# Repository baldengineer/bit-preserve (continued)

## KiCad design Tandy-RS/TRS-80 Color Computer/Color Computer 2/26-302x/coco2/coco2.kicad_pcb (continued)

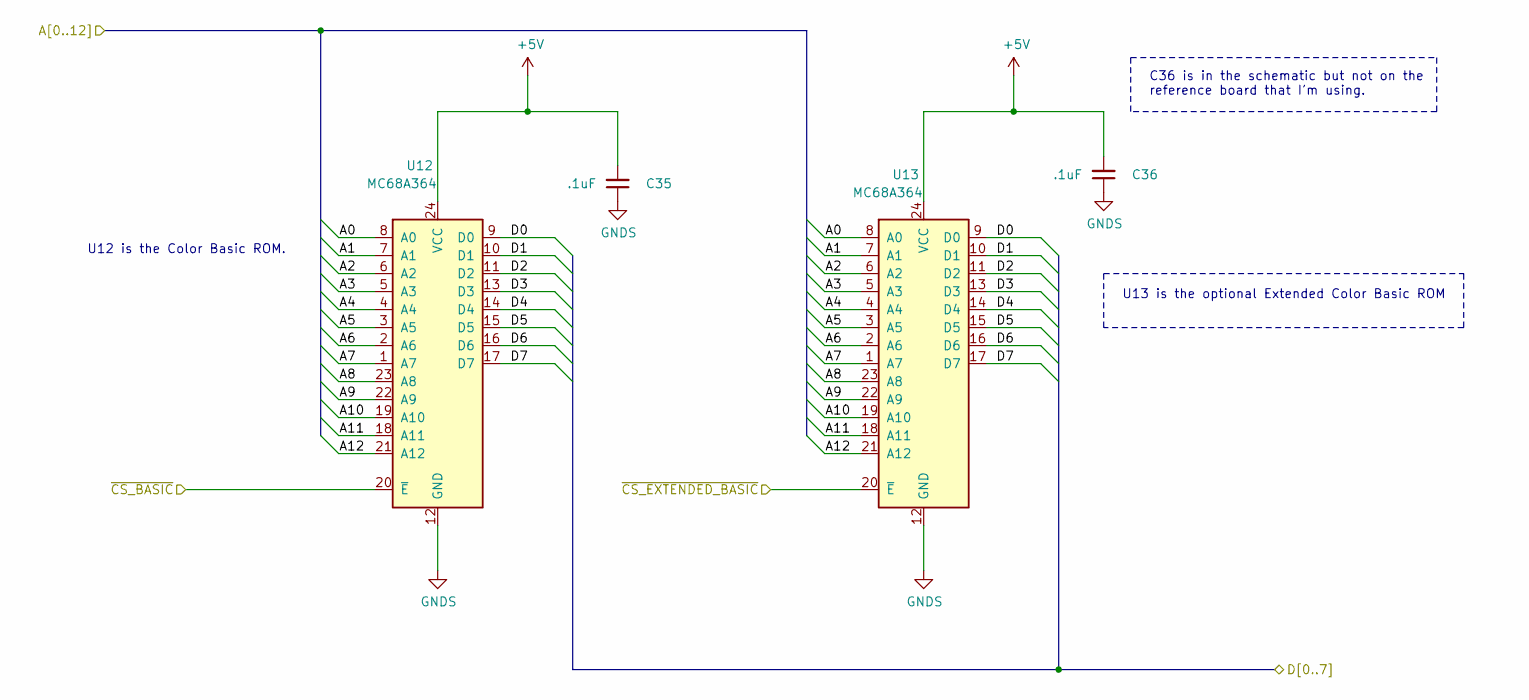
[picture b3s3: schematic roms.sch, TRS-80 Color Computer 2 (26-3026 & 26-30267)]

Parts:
C35, C36: .1uF; C_Axial_L3.8mm_D2.6mm_P10.00mm_Horizontal; Manufacturer part# A104K15X7RF5TAA
U12, U13: MC68A364; DIP-24_W15.24mm_Socket; Manufacturer part# 243-24-1-06

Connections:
+5V: C35.2, C36.2, U12.24 (VCC), U13.24 (VCC); also elsewhere on the board
/A0: U12.8 (A0), U13.8 (A0); also elsewhere on the board
/A1: U12.7 (A1), U13.7 (A1); also elsewhere on the board
/A2: U12.6 (A2), U13.6 (A2); also elsewhere on the board
/A3: U12.5 (A3), U13.5 (A3); also elsewhere on the board
/A4: U12.4 (A4), U13.4 (A4); also elsewhere on the board
/A5: U12.3 (A5), U13.3 (A5); also elsewhere on the board
/A6: U12.2 (A6), U13.2 (A6); also elsewhere on the board
/A7: U12.1 (A7), U13.1 (A7); also elsewhere on the board
/A8: U12.23 (A8), U13.23 (A8); also elsewhere on the board
/A9: U12.22 (A9), U13.22 (A9); also elsewhere on the board
/A10: U12.19 (A10), U13.19 (A10); also elsewhere on the board
/A11: U12.18 (A11), U13.18 (A11); also elsewhere on the board
/A12: U12.21 (A12), U13.21 (A12); also elsewhere on the board
/D0: U12.9 (D0), U13.9 (D0); also elsewhere on the board
/D1: U12.10 (D1), U13.10 (D1); also elsewhere on the board
/D2: U12.11 (D2), U13.11 (D2); also elsewhere on the board
/D3: U12.13 (D3), U13.13 (D3); also elsewhere on the board
/D4: U12.14 (D4), U13.14 (D4); also elsewhere on the board
/D5: U12.15 (D5), U13.15 (D5); also elsewhere on the board
/D6: U12.16 (D6), U13.16 (D6); also elsewhere on the board
/D7: U12.17 (D7), U13.17 (D7); also elsewhere on the board
/roms/~CS_BASIC: U12.20 (~E); also elsewhere on the board
/roms/~CS_EXTENDED_BASIC: U13.20 (~E); also elsewhere on the board
GNDS: C35.1, C36.1, U12.12 (GND), U13.12 (GND); also elsewhere on the board

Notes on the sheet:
U12 is the Color Basic ROM.
U13 is the optional Extended Color Basic ROM
C36 is in the schematic but not on the reference board that I'm using.

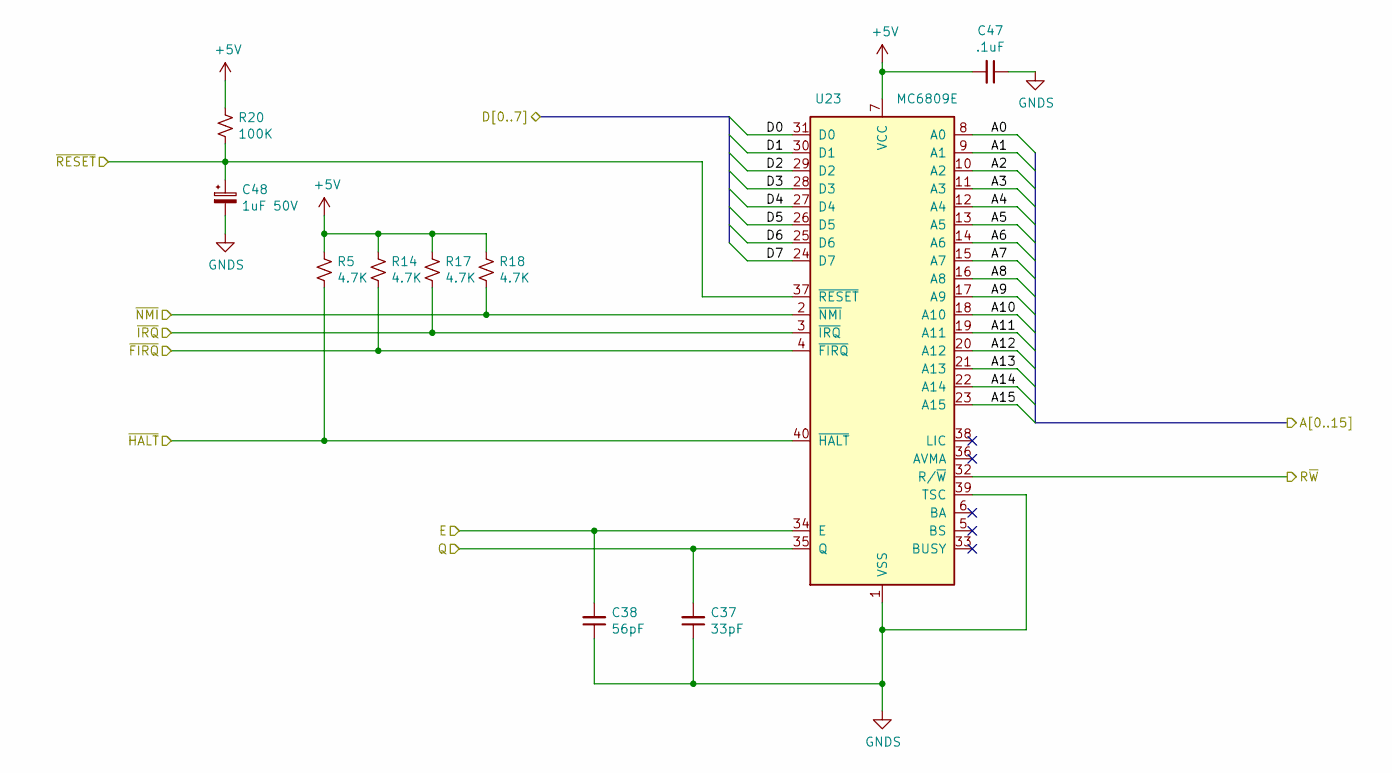
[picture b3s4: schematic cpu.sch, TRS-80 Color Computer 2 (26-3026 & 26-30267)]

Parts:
C37: 33pF; C_Rect_L7.2mm_W3.0mm_P5.00mm_FKS2_FKP2_MKS2_MKP2; Manufacturer part# FA28NP01H330JNU06
C38: 56pF; C_Rect_L7.2mm_W2.5mm_P5.00mm_FKS2_FKP2_MKS2_MKP2; Manufacturer part# RDE5C1H560J0M1H03A
C47: .1uF; C_Axial_L3.8mm_D2.6mm_P10.00mm_Horizontal; Manufacturer part# A104K15X7RF5TAA
C48: 1uF 50V; CP_Radial_D5.0mm_P2.00mm; Manufacturer part# 515D105M050JA6AE3
R5, R14, R17, R18: 4.7K; R_Axial_DIN0207_L6.3mm_D2.5mm_P10.16mm_Horizontal; Manufacturer part# Stackpole Electronics Inc
R20: 100K; R_Axial_DIN0207_L6.3mm_D2.5mm_P10.16mm_Horizontal
U23: MC6809E; DIP-40_W15.24mm_Socket; Manufacturer part# ED40DT

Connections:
+5V: C47.2, R5.1, R14.1, R17.1, R18.1, R20.1, U23.7 (VCC); also elsewhere on the board
/A0: U23.8 (A0); also elsewhere on the board
/A1: U23.9 (A1); also elsewhere on the board
/A2: U23.10 (A2); also elsewhere on the board
/A3: U23.11 (A3); also elsewhere on the board
/A4: U23.12 (A4); also elsewhere on the board
/A5: U23.13 (A5); also elsewhere on the board
/A6: U23.14 (A6); also elsewhere on the board
/A7: U23.15 (A7); also elsewhere on the board
/A8: U23.16 (A8); also elsewhere on the board
/A9: U23.17 (A9); also elsewhere on the board
/A10: U23.18 (A10); also elsewhere on the board
/A11: U23.19 (A11); also elsewhere on the board
/A12: U23.20 (A12); also elsewhere on the board
/A13: U23.21 (A13); also elsewhere on the board
/A14: U23.22 (A14); also elsewhere on the board
/A15: U23.23 (A15); also elsewhere on the board
/D0: U23.31 (D0); also elsewhere on the board
/D1: U23.30 (D1); also elsewhere on the board
/D2: U23.29 (D2); also elsewhere on the board
/D3: U23.28 (D3); also elsewhere on the board
/D4: U23.27 (D4); also elsewhere on the board
/D5: U23.26 (D5); also elsewhere on the board
/D6: U23.25 (D6); also elsewhere on the board
/D7: U23.24 (D7); also elsewhere on the board
/E: C38.2, U23.34 (E); also elsewhere on the board
/Q: C37.2, U23.35 (Q); also elsewhere on the board
/R~W: U23.32 (R/~W); also elsewhere on the board
/~FIRQ: R14.2, U23.4 (~FIRQ); also elsewhere on the board
/~HALT: R5.2, U23.40 (~HALT); also elsewhere on the board
/~IRQ: R17.2, U23.3 (~IRQ); also elsewhere on the board
/~NMI: R18.2, U23.2 (~NMI); also elsewhere on the board
/~RESET: C48.1, R20.2, U23.37 (~RESET); also elsewhere on the board
GNDS: C37.1, C38.1, C47.1, C48.2, U23.1 (VSS), U23.39 (TSC); also elsewhere on the board

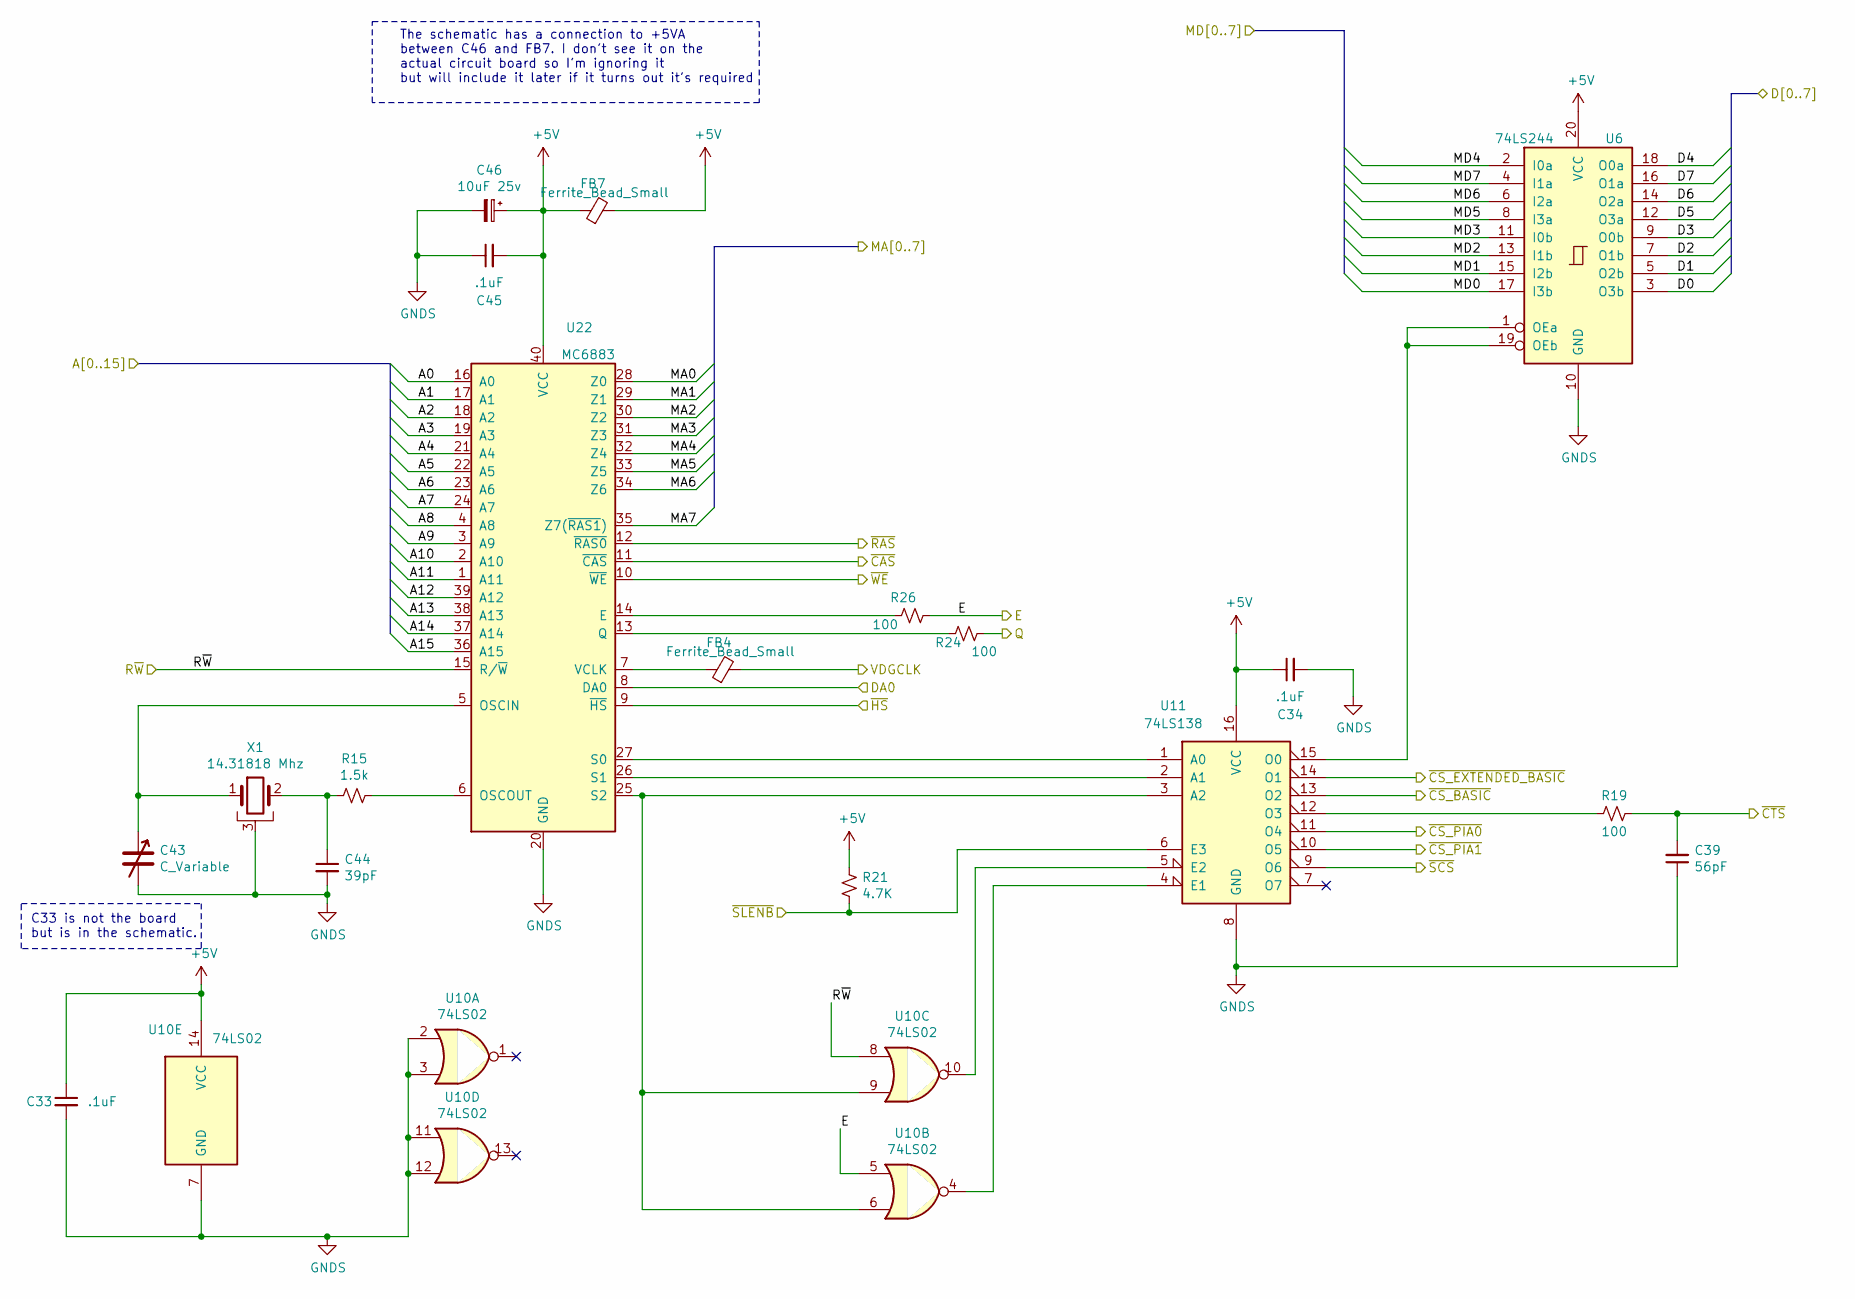
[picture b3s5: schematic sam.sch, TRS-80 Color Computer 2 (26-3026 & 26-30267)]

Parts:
C33, C34, C45: .1uF; C_Axial_L3.8mm_D2.6mm_P10.00mm_Horizontal; Manufacturer part# A104K15X7RF5TAA
C39: 56pF; C_Rect_L7.2mm_W2.5mm_P5.00mm_FKS2_FKP2_MKS2_MKP2; Manufacturer part# RDE5C1H560J0M1H03A
C43: C_Variable; C_Rect_L7.2mm_W7.2mm_P5.00mm_FKS2_FKP2_MKS2_MKP2; Manufacturer part# GKG50015
C44: 39pF; C_Disc_D7.5mm_W5.0mm_P5.00mm; Manufacturer part# RDE5C1H390J0M1H03A
C46: 10uF 25v; CP_Radial_D5.0mm_P2.00mm; Manufacturer part# UPW1E100MDD
FB4, FB7: Ferrite_Bead_Small; ferrite_bead; Manufacturer part# 2743007111
R15: 1.5k; R_Axial_DIN0207_L6.3mm_D2.5mm_P10.16mm_Horizontal; Manufacturer part# MFR-25FBF52-1K5
R19, R24, R26: 100; R_Axial_DIN0207_L6.3mm_D2.5mm_P10.16mm_Horizontal; Manufacturer part# MFR-25FBF52-100R
R21: 4.7K; R_Axial_DIN0207_L6.3mm_D2.5mm_P10.16mm_Horizontal; Manufacturer part# Stackpole Electronics Inc
U6: 74LS244; DIP-20_W7.62mm_Socket; Manufacturer part# 243-20-1-03
U10: 74LS02; DIP-14_W7.62mm_Socket; Manufacturer part# 1-2199298-4
U11: 74LS138; DIP-16_W7.62mm_Socket; Manufacturer part# 1-2199298-4
U22: MC6883; DIP-40_W15.24mm_Socket; Manufacturer part# ED40DT
X1: 14.31818 Mhz; Crystal_HC49-U_Horizontal; Manufacturer part# MP143

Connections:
+5V: C33.1, C34.1, C45.2, C46.1, FB7.1, FB7.2, R21.1, U6.20 (VCC), U10.14 (VCC), U11.16 (VCC), U22.40 (VCC); also elsewhere on the board
/A0: U22.16 (A0); also elsewhere on the board
/A1: U22.17 (A1); also elsewhere on the board
/A2: U22.18 (A2); also elsewhere on the board
/A3: U22.19 (A3); also elsewhere on the board
/A4: U22.21 (A4); also elsewhere on the board
/A5: U22.22 (A5); also elsewhere on the board
/A6: U22.23 (A6); also elsewhere on the board
/A7: U22.24 (A7); also elsewhere on the board
/A8: U22.4 (A8); also elsewhere on the board
/A9: U22.3 (A9); also elsewhere on the board
/A10: U22.2 (A10); also elsewhere on the board
/A11: U22.1 (A11); also elsewhere on the board
/A12: U22.39 (A12); also elsewhere on the board
/A13: U22.38 (A13); also elsewhere on the board
/A14: U22.37 (A14); also elsewhere on the board
/A15: U22.36 (A15); also elsewhere on the board
/D0: U6.3 (O3b); also elsewhere on the board
/D1: U6.5 (O2b); also elsewhere on the board
/D2: U6.7 (O1b); also elsewhere on the board
/D3: U6.9 (O0b); also elsewhere on the board
/D4: U6.18 (O0a); also elsewhere on the board
/D5: U6.12 (O3a); also elsewhere on the board
/D6: U6.14 (O2a); also elsewhere on the board
/D7: U6.16 (O1a); also elsewhere on the board
/E: R26.1, U10.5; also elsewhere on the board
/Q: R24.1; also elsewhere on the board
/R~W: U10.8, U22.15 (R/~W); also elsewhere on the board
/dram/MA0: U22.28 (Z0); also elsewhere on the board
/dram/MA1: U22.29 (Z1); also elsewhere on the board
/dram/MA2: U22.30 (Z2); also elsewhere on the board
/dram/MA3: U22.31 (Z3); also elsewhere on the board
/dram/MA4: U22.32 (Z4); also elsewhere on the board
/dram/MA5: U22.33 (Z5); also elsewhere on the board
/dram/MA6: U22.34 (Z6); also elsewhere on the board
/dram/MA7: U22.35 (Z7(~RAS1~)); also elsewhere on the board
/dram/MD0: U6.17 (I3b); also elsewhere on the board
/dram/MD1: U6.15 (I2b); also elsewhere on the board
/dram/MD2: U6.13 (I1b); also elsewhere on the board
/dram/MD3: U6.11 (I0b); also elsewhere on the board
/dram/MD4: U6.2 (I0a); also elsewhere on the board
/dram/MD5: U6.8 (I3a); also elsewhere on the board
/dram/MD6: U6.6 (I2a); also elsewhere on the board
/dram/MD7: U6.4 (I1a); also elsewhere on the board
/dram/~CAS: U22.11 (~CAS); also elsewhere on the board
/dram/~RAS: U22.12 (~RAS0); also elsewhere on the board
/dram/~WE: U22.10 (~WE); also elsewhere on the board
/power/VDGCLK: FB4.2; also elsewhere on the board
/roms/~CS_BASIC: U11.13 (O2); also elsewhere on the board
/roms/~CS_EXTENDED_BASIC: U11.14 (O1); also elsewhere on the board
/sam/DA0: U22.8 (DA0); also elsewhere on the board
/~CSPIA1: U11.10 (O5); also elsewhere on the board
/~CS_PIA0: U11.11 (O4); also elsewhere on the board
/~CTS: C39.2, R19.1; also elsewhere on the board
/~HS: U22.9 (~HS); also elsewhere on the board
/~SCS: U11.9 (O6); also elsewhere on the board
/~SLENB: R21.2, U11.6 (E3); also elsewhere on the board
GNDS: C33.2, C34.2, C39.1, C43.2, C44.2, C45.1, C46.2, U6.10 (GND), U10.2, U10.3, U10.7 (GND), U10.11, U10.12, U11.8 (GND), U22.20 (GND), X1.3; also elsewhere on the board
unnamed: C43.1, U22.5 (OSCIN), X1.1
unnamed: C44.1, R15.2, X1.2
unnamed: FB4.1, U22.7 (VCLK)
unnamed: R15.1, U22.6 (OSCOUT)
unnamed: R19.2, U11.12 (O3)
unnamed: R24.2, U22.13 (Q)
unnamed: R26.2, U22.14 (E)
unnamed: U10.4, U11.4 (E1)
unnamed: U10.6, U10.9, U11.3 (A2), U22.25 (S2)
unnamed: U10.10, U11.5 (E2)
unnamed: U11.1 (A0), U22.27 (S0)
unnamed: U11.2 (A1), U22.26 (S1)
unnamed: U6.1 (OEa), U6.19 (OEb), U11.15 (O0)

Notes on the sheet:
The schematic has a connection to +5VA between C46 and FB7. I don't see it on the actual circuit board so I'm ignoring it but will include it later if it turns out it's required
C33 is not the board but is in the schematic.

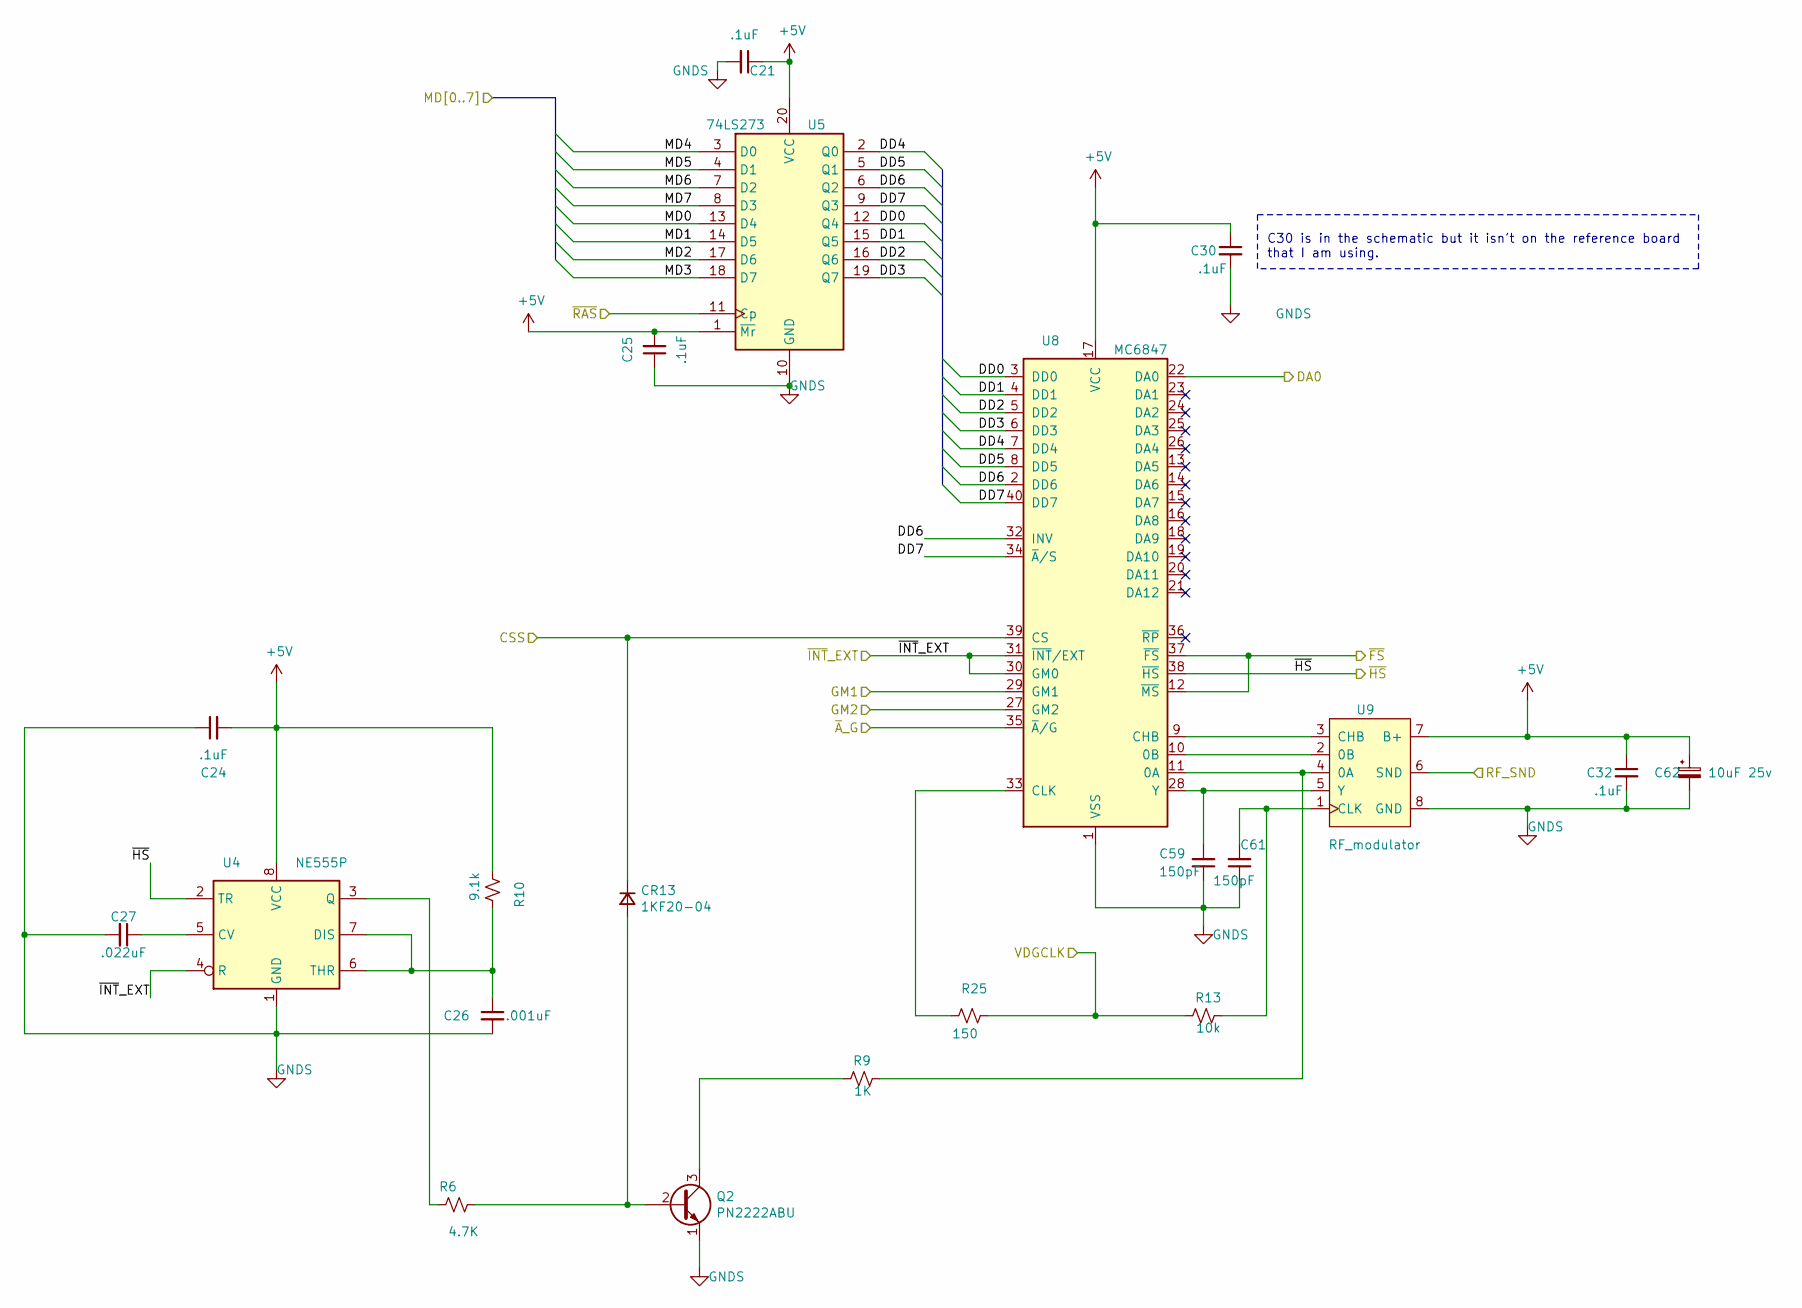
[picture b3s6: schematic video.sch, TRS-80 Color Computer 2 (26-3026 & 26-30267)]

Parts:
C21, C24, C25, C30, C32: .1uF; C_Axial_L3.8mm_D2.6mm_P10.00mm_Horizontal; Manufacturer part# A104K15X7RF5TAA
C26: .001uF; C_Rect_L4.0mm_W2.5mm_P2.50mm; Manufacturer part# C315C102K1R5TA7301
C27: .022uF; C_Disc_D8.0mm_W2.5mm_P5.00mm; Manufacturer part# C317C223M5U5TA7301
C59, C61: 150pF; C_Rect_L7.2mm_W2.5mm_P5.00mm_FKS2_FKP2_MKS2_MKP2; Manufacturer part# FA28C0G2E151JNU06
C62: 10uF 25v; CP_Radial_D5.0mm_P2.00mm; Manufacturer part# UPW1E100MDD
CR13: 1KF20-04; D_A-405_P10.16mm_Horizontal; Manufacturer part# D-GE-GEN PURP 75V
Q2: PN2222ABU; TO-92_Inline; Manufacturer part# PN2222ABU
R6: 4.7K; R_Axial_DIN0207_L6.3mm_D2.5mm_P10.16mm_Horizontal; Manufacturer part# Stackpole Electronics Inc
R9: 1K; R_Axial_DIN0207_L6.3mm_D2.5mm_P10.16mm_Horizontal; Manufacturer part# CF14JT1K00
R10: 9.1k; R_Axial_DIN0207_L6.3mm_D2.5mm_P10.16mm_Horizontal; Manufacturer part# CF14JT9K10
R13: 10k; R_Axial_DIN0207_L6.3mm_D2.5mm_P10.16mm_Horizontal; Manufacturer part# CF14JT10K0
R25: 150; R_Axial_DIN0207_L6.3mm_D2.5mm_P10.16mm_Horizontal; Manufacturer part# CF14JT150R
U4: NE555P; DIP-8_W7.62mm_Socket; Manufacturer part# A 08-LC-TT
U5: 74LS273; DIP-20_W7.62mm_Socket; Manufacturer part# 243-20-1-03
U8: MC6847; DIP-40_W15.24mm_Socket; Manufacturer part# ED40DT
U9: RF_modulator; coco2_vertical_rf_sheild_3

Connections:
+5V: C21.1, C24.2, C25.2, C30.1, C32.1, C62.1, R10.2, U4.8 (VCC), U5.1 (~Mr), U5.20 (VCC), U8.17 (VCC), U9.7 (B+); also elsewhere on the board
/dram/MD0: U5.13 (D4); also elsewhere on the board
/dram/MD1: U5.14 (D5); also elsewhere on the board
/dram/MD2: U5.17 (D6); also elsewhere on the board
/dram/MD3: U5.18 (D7); also elsewhere on the board
/dram/MD4: U5.3 (D0); also elsewhere on the board
/dram/MD5: U5.4 (D1); also elsewhere on the board
/dram/MD6: U5.7 (D2); also elsewhere on the board
/dram/MD7: U5.8 (D3); also elsewhere on the board
/dram/~RAS: U5.11 (Cp); also elsewhere on the board
/peripherals/CSS: CR13.1 (K), U8.39 (CS); also elsewhere on the board
/peripherals/GM1: U8.29 (GM1); also elsewhere on the board
/peripherals/GM2: U8.27 (GM2); also elsewhere on the board
/peripherals/~A~_G: U8.35 (~A~/G); also elsewhere on the board
/peripherals/~INT~_EXT: U4.4 (R), U8.30 (GM0), U8.31 (~INT~/EXT); also elsewhere on the board
/power/VDGCLK: R13.2, R25.1; also elsewhere on the board
/sam/DA0: U8.22 (DA0); also elsewhere on the board
/video/DD0: U5.12 (Q4), U8.3 (DD0)
/video/DD1: U5.15 (Q5), U8.4 (DD1)
/video/DD2: U5.16 (Q6), U8.5 (DD2)
/video/DD3: U5.19 (Q7), U8.6 (DD3)
/video/DD4: U5.2 (Q0), U8.7 (DD4)
/video/DD5: U5.5 (Q1), U8.8 (DD5)
/video/DD6: U5.6 (Q2), U8.2 (DD6), U8.32 (INV)
/video/DD7: U5.9 (Q3), U8.34 (~A~/S), U8.40 (DD7)
/video/RF_SND: U9.6 (SND); also elsewhere on the board
/~FS: U8.12 (~MS), U8.37 (~FS); also elsewhere on the board
/~HS: U4.2 (TR), U8.38 (~HS); also elsewhere on the board
GNDS: C21.2, C24.1, C25.1, C26.2, C27.2, C30.2, C32.2, C59.1, C61.1, C62.2, Q2.1 (E), U4.1 (GND), U5.10 (GND), U8.1 (VSS), U9.8 (GND); also elsewhere on the board
unnamed: C26.1, R10.1, U4.6 (THR), U4.7 (DIS)
unnamed: C27.1, U4.5 (CV)
unnamed: C59.2, U8.28 (Y), U9.5 (Y)
unnamed: C61.2, R13.1, U9.1 (CLK)
unnamed: CR13.2 (A), Q2.2 (B), R6.1
unnamed: Q2.3 (C), R9.2
unnamed: R6.2, U4.3 (Q)
unnamed: R9.1, U8.11 (0A), U9.4 (0A)
unnamed: R25.2, U8.33 (CLK)
unnamed: U8.9 (CHB), U9.3 (CHB)
unnamed: U8.10 (0B), U9.2 (0B)

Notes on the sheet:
C30 is in the schematic but it isn't on the reference board that I am using.

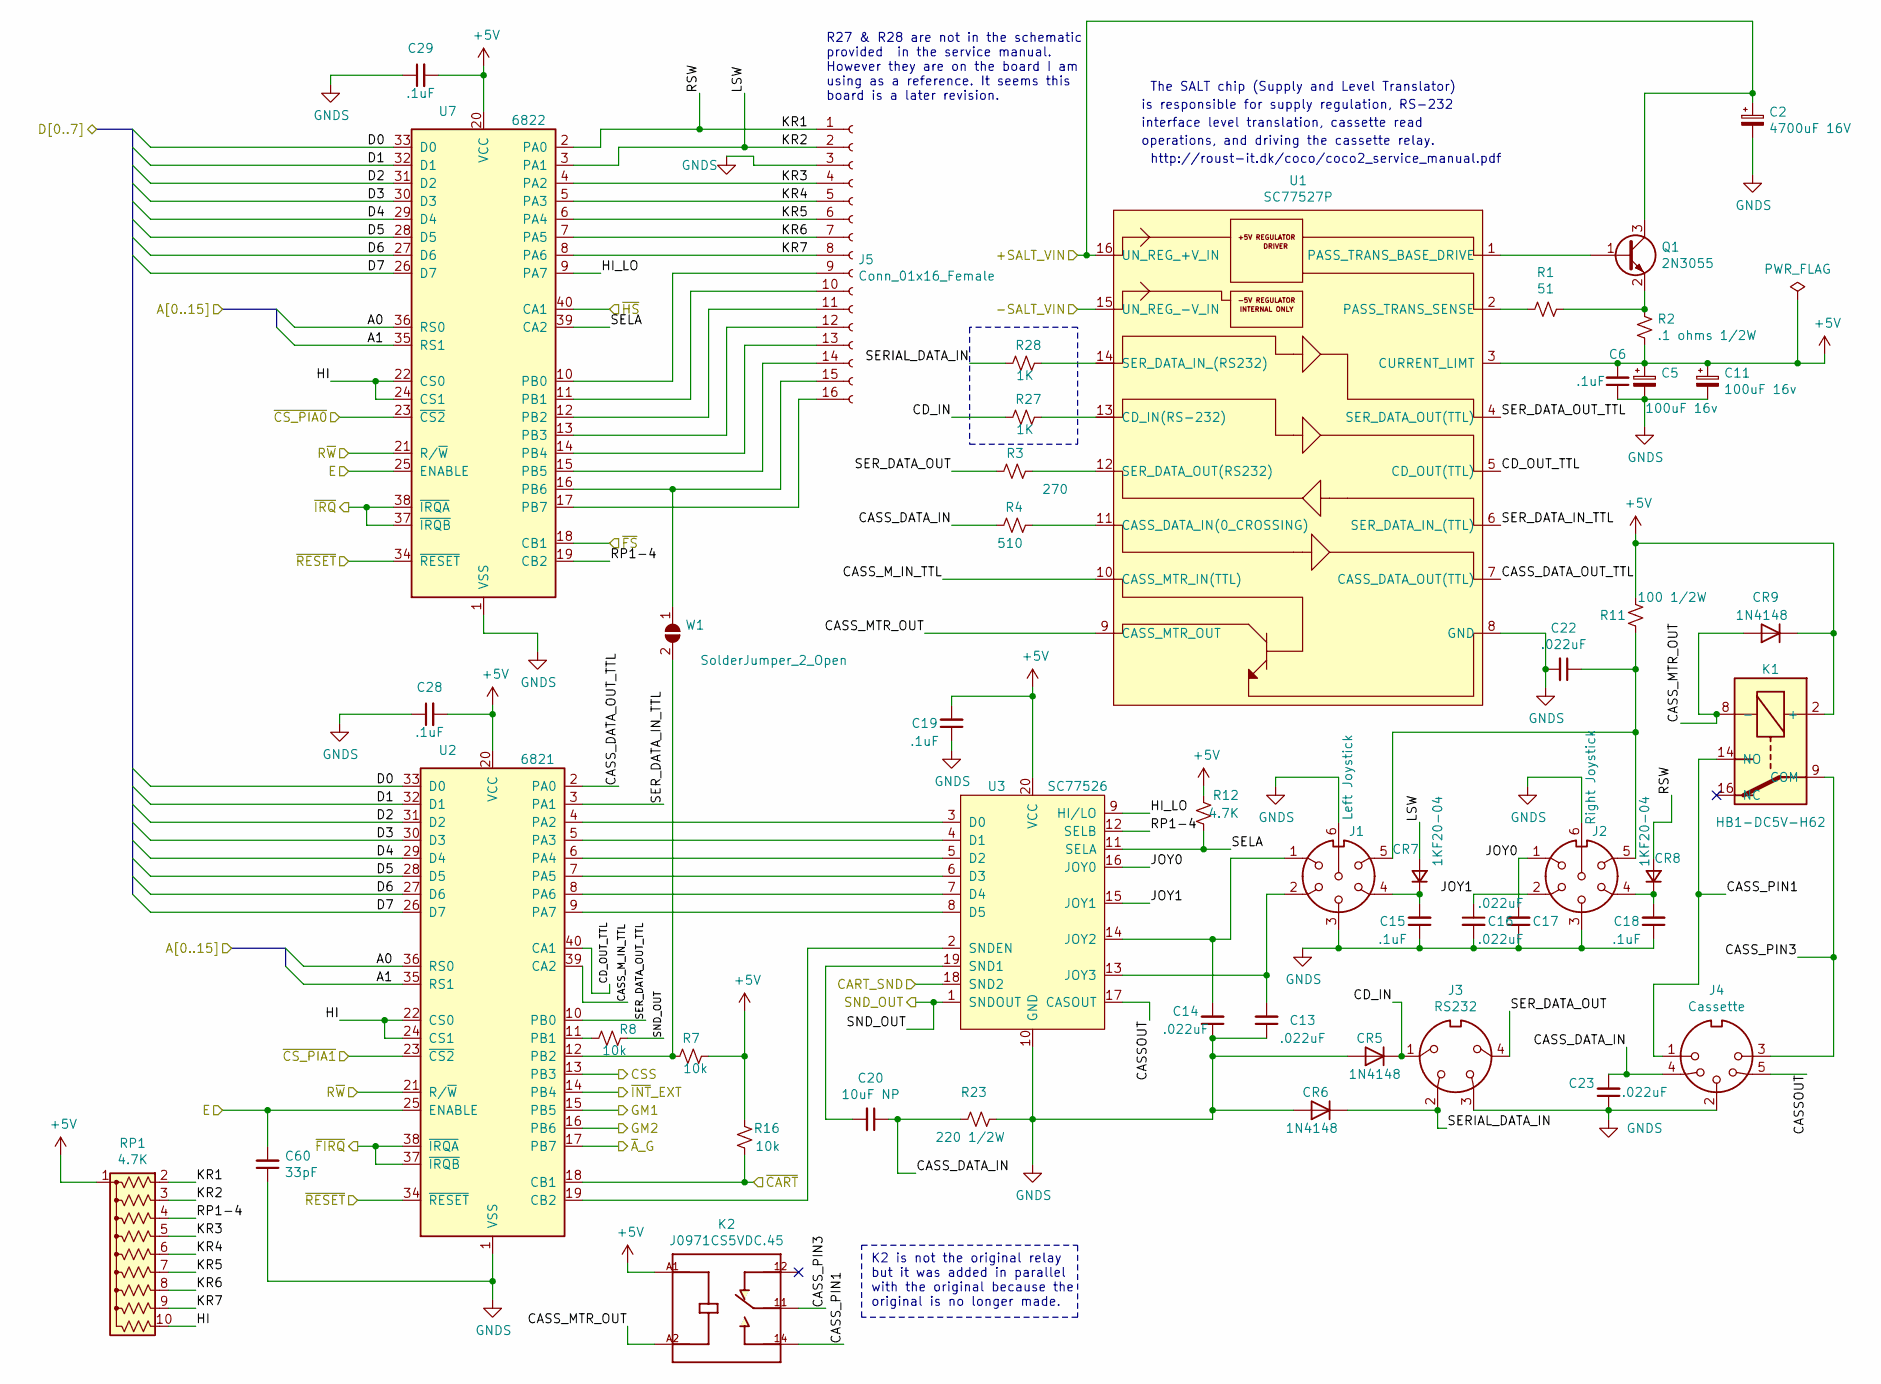
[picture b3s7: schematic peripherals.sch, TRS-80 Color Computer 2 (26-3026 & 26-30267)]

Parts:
C2: 4700uF 16V; CP_Radial_D16.0mm_P7.50mm; Manufacturer part# 16YXJ4700M16X25
C5, C11: 100uF 16v; CP_Radial_D8.0mm_P5.00mm; Manufacturer part# UST1C101MDD1TA
C6, C15, C18, C19, C28, C29: .1uF; C_Axial_L3.8mm_D2.6mm_P10.00mm_Horizontal; Manufacturer part# A104K15X7RF5TAA
C13, C14, C16, C17, C22, C23: .022uF; C_Disc_D8.0mm_W2.5mm_P5.00mm; Manufacturer part# C317C223M5U5TA7301
C20: 10uF NP; C_Radial_D5.0mm_H11.0mm_P2.00mm; Manufacturer part# UES1E100MDM1TD
C60: 33pF; C_Rect_L7.2mm_W3.0mm_P5.00mm_FKS2_FKP2_MKS2_MKP2; Manufacturer part# FA28NP01H330JNU06
CR5, CR6, CR9: 1N4148; D_DO-35_SOD27_P7.62mm_Horizontal; Manufacturer part# 1N4148
CR7, CR8: 1KF20-04; D_A-405_P10.16mm_Horizontal; Manufacturer part# D-GE-GEN PURP 75V
J1: Left Joystick; CUI_SDS-60J; Manufacturer part# SDS-60J
J2: Right Joystick; CUI_SDS-60J; Manufacturer part# SDS-60J
J3: RS232; CUI_SDS-40J; Manufacturer part# SDS-40J
J4: Cassette; CUI_SDS-50J; Manufacturer part# SDS-50J
J5: Conn_01x16_Female; PinHeader_1x16_P2.54mm_Vertical; Manufacturer part# 6-520415-6
K1: HB1-DC5V-H62; HB1-DC5V-H62_W7.62mm
K2: J0971CS5VDC.45; RELAY_J0971CS5VDC.45; Manufacturer part# J0971CS5VDC.45
Q1: 2N3055; TO-3; Manufacturer part# 2N3055
R1: 51; R_Axial_DIN0207_L6.3mm_D2.5mm_P10.16mm_Horizontal; Manufacturer part# CF1/4CT52R510J
R2: .1 ohms 1/2W; R_Axial_DIN0411_L9.9mm_D3.6mm_P15.24mm_Horizontal; Manufacturer part# LR1LJR10
R3: 270; R_Axial_DIN0207_L6.3mm_D2.5mm_P10.16mm_Horizontal; Manufacturer part# CF14JT270R
R4: 510; R_Axial_DIN0207_L6.3mm_D2.5mm_P10.16mm_Horizontal; Manufacturer part# CF14JT510R
R7, R8, R16: 10k; R_Axial_DIN0207_L6.3mm_D2.5mm_P10.16mm_Horizontal; Manufacturer part# CF14JT10K0
R11: 100 1/2W; R_Axial_DIN0411_L9.9mm_D3.6mm_P12.70mm_Horizontal; Manufacturer part# CF12JT100R
R12: 4.7K; R_Axial_DIN0207_L6.3mm_D2.5mm_P10.16mm_Horizontal; Manufacturer part# Stackpole Electronics Inc
R23: 220 1/2W; R_Axial_DIN0411_L9.9mm_D3.6mm_P12.70mm_Horizontal; Manufacturer part# CF12JT220R
R27, R28: 1K; R_Axial_DIN0207_L6.3mm_D2.5mm_P10.16mm_Horizontal; Manufacturer part# CF14JT1K00
RP1: 4.7K; R_Array_SIP10; Manufacturer part# 4610X-101-472LF
U1: SC77527P; DIP-16_W7.62mm_Socket; Manufacturer part# 1-2199298-4
U2: 6821; DIP-40_W15.24mm_Socket; Manufacturer part# ED40DT
U3: SC77526; DIP-20_W7.62mm_Socket; Manufacturer part# 243-20-1-03
U7: 6822; DIP-40_W15.24mm_Socket; Manufacturer part# ED40DT
W1: SolderJumper_2_Open; SolderJumper-2_P1.3mm_Open_RoundedPad1.0x1.5mm

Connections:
+5V: C5.1, C6.2, C11.1, C19.2, C28.2, C29.2, CR9.1 (K), K1.2 (+), K2.A1, R2.1, R7.1, R11.1, R12.2, R16.2, RP1.1 (common), U1.3 (CURRENT_LIMT), U2.20 (VCC), U3.20 (VCC), U7.20 (VCC); also elsewhere on the board
/A0: U2.36 (RS0), U7.36 (RS0); also elsewhere on the board
/A1: U2.35 (RS1), U7.35 (RS1); also elsewhere on the board
/CART_SND: U3.18 (SND2); also elsewhere on the board
/D0: U2.33 (D0), U7.33 (D0); also elsewhere on the board
/D1: U2.32 (D1), U7.32 (D1); also elsewhere on the board
/D2: U2.31 (D2), U7.31 (D2); also elsewhere on the board
/D3: U2.30 (D3), U7.30 (D3); also elsewhere on the board
/D4: U2.29 (D4), U7.29 (D4); also elsewhere on the board
/D5: U2.28 (D5), U7.28 (D5); also elsewhere on the board
/D6: U2.27 (D6), U7.27 (D6); also elsewhere on the board
/D7: U2.26 (D7), U7.26 (D7); also elsewhere on the board
/E: C60.2, U2.25 (ENABLE), U7.25 (ENABLE); also elsewhere on the board
/R~W: U2.21 (R/~W), U7.21 (R/~W); also elsewhere on the board
/peripherals/+SALT_VIN: C2.1, Q1.3 (C), U1.16 (UN_REG_+V_IN); also elsewhere on the board
/peripherals/-SALT_VIN: U1.15 (UN_REG_-V_IN); also elsewhere on the board
/peripherals/CASSOUT: J4.5, U3.17 (CASOUT)
/peripherals/CASS_DATA_IN: C20.1, C23.2, J4.4, R4.1, R23.2
/peripherals/CASS_DATA_OUT_TTL: U1.7 (CASS_DATA_OUT(TTL)), U2.2 (PA0)
/peripherals/CASS_MTR_OUT: CR9.2 (A), K1.8 (-), K2.A2, U1.9 (CASS_MTR_OUT)
/peripherals/CASS_M_IN_TTL: U1.10 (CASS_MTR_IN(TTL)), U2.39 (CA2)
/peripherals/CASS_PIN1: J4.1, K1.14 (NO), K2.14
/peripherals/CASS_PIN3: J4.3, K1.9 (COM), K2.11
/peripherals/CD_IN: CR5.1 (K), J3.1, R27.2
/peripherals/CD_OUT_TTL: U1.5 (CD_OUT(TTL)), U2.40 (CA1)
/peripherals/CSS: U2.13 (PB3); also elsewhere on the board
/peripherals/GM1: U2.15 (PB5); also elsewhere on the board
/peripherals/GM2: U2.16 (PB6); also elsewhere on the board
/peripherals/HI: RP1.10 (R9), U2.22 (CS0), U2.24 (CS1), U7.22 (CS0), U7.24 (CS1)
/peripherals/HI_LO: U3.9 (HI/LO), U7.9 (PA7)
/peripherals/JOY0: C17.2, J2.1, U3.16 (JOY0)
/peripherals/JOY1: C16.1, J2.2, U3.15 (JOY1)
/peripherals/KR1: CR8.2 (A), J5.1, RP1.2 (R1), U7.2 (PA0)
/peripherals/KR2: CR7.2 (A), J5.2, RP1.3 (R2), U7.3 (PA1)
/peripherals/KR3: J5.4, RP1.5 (R4), U7.4 (PA2)
/peripherals/KR4: J5.5, RP1.6 (R5), U7.5 (PA3)
/peripherals/KR5: J5.6, RP1.7 (R6), U7.6 (PA4)
/peripherals/KR6: J5.7, RP1.8 (R7), U7.7 (PA5)
/peripherals/KR7: J5.8, RP1.9 (R8), U7.8 (PA6)
/peripherals/RP1-4: RP1.4 (R3), U3.12 (SELB), U7.19 (CB2)
/peripherals/SELA: R12.1, U3.11 (SELA), U7.39 (CA2)
/peripherals/SERIAL_DATA_IN: CR6.1 (K), J3.2, R28.2
/peripherals/SER_DATA_IN_TTL: U1.6 (SER_DATA_IN_(TTL)), U2.3 (PA1)
/peripherals/SER_DATA_OUT: J3.4, R3.2
/peripherals/SER_DATA_OUT_TTL: U1.4 (SER_DATA_OUT(TTL)), U2.10 (PB0)
/peripherals/~A~_G: U2.17 (PB7); also elsewhere on the board
/peripherals/~INT~_EXT: U2.14 (PB4); also elsewhere on the board
/video/RF_SND: R8.1, U3.1 (SNDOUT); also elsewhere on the board
/~CART: R16.1, U2.18 (CB1); also elsewhere on the board
/~CSPIA1: U2.23 (~CS2); also elsewhere on the board
/~CS_PIA0: U7.23 (~CS2); also elsewhere on the board
/~FIRQ: U2.37 (~IRQB), U2.38 (~IRQA); also elsewhere on the board
/~FS: U7.18 (CB1); also elsewhere on the board
/~HS: U7.40 (CA1); also elsewhere on the board
/~IRQ: U7.37 (~IRQB), U7.38 (~IRQA); also elsewhere on the board
/~RESET: U2.34 (~RESET), U7.34 (~RESET); also elsewhere on the board
GNDS: C2.2, C5.2, C6.1, C11.2, C13.1, C14.1, C15.1, C16.2, C17.1, C18.1, C19.1, C22.2, C23.1, C28.1, C29.1, C60.1, CR5.2 (A), CR6.2 (A), J1.3, J1.6, J2.3, J2.6, J3.3, J4.2, J5.3, R23.1, U1.8 (GND), U2.1 (VSS), U3.10 (GND), U7.1 (VSS); also elsewhere on the board
unnamed: C13.2, J1.2, U3.13 (JOY3)
unnamed: C14.2, J1.1, U3.14 (JOY2)
unnamed: C15.2, CR7.1 (K), J1.4
unnamed: C18.2, CR8.1 (K), J2.4
unnamed: C20.2, U3.19 (SND1)
unnamed: C22.1, J1.5, J2.5, R11.2
unnamed: J5.9, U7.10 (PB0)
unnamed: J5.10, U7.11 (PB1)
unnamed: J5.11, U7.12 (PB2)
unnamed: J5.12, U7.13 (PB3)
unnamed: J5.13, U7.14 (PB4)
unnamed: J5.14, U7.15 (PB5)
unnamed: J5.15, U7.16 (PB6), W1.1 (A)
unnamed: J5.16, U7.17 (PB7)
unnamed: Q1.1 (B), U1.1 (PASS_TRANS_BASE_DRIVE)
unnamed: Q1.2 (E), R1.1, R2.2
unnamed: R1.2, U1.2 (PASS_TRANS_SENSE)
unnamed: R3.1, U1.12 (SER_DATA_OUT(RS232))
unnamed: R4.2, U1.11 (CASS_DATA_IN(0_CROSSING))
unnamed: R7.2, U2.12 (PB2), W1.2 (B)
unnamed: R8.2, U2.11 (PB1)
unnamed: R27.1, U1.13 (CD_IN(RS-232))
unnamed: R28.1, U1.14 (SER_DATA_IN_(RS232))
unnamed: U2.4 (PA2), U3.3 (D0)
unnamed: U2.5 (PA3), U3.4 (D1)
unnamed: U2.6 (PA4), U3.5 (D2)
unnamed: U2.7 (PA5), U3.6 (D3)
unnamed: U2.8 (PA6), U3.7 (D4)
unnamed: U2.9 (PA7), U3.8 (D5)
unnamed: U2.19 (CB2), U3.2 (SNDEN)

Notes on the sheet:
The SALT chip (Supply and Level Translator)
is responsible for supply regulation, RS-232
interface level translation, cassette read
operations, and driving the cassette relay.
http://roust-it.dk/coco/coco2_service_manual.pdf
R27 & R28 are not in the schematic provided in the service manual. However they are on the board I am using as a reference. It seems this board is a later revision.
K2 is not the original relay but it was added in parallel with the original because the original is no longer made.
